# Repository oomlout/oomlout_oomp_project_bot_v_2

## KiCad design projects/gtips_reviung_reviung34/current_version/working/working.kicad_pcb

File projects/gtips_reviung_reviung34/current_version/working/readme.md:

# reviung
 
## summary 
* id: gtips_reviung_reviung34
* user: gtips
* name: reviung
* board: reviung34
* repo: https://github.com/gtips/reviung
* src_file_repo_kicad_pcb: reviung34/pcb/reviung34.kicad_pcb
* src_file_repo_kicad_pcb_link: https://github.com/gtips/reviung/tree/master/reviung34/pcb/reviung34.kicad_pcb

* src_file_repo_sch: reviung34/pcb/reviung34.sch
* src_file_repo_sch_link: https://github.com/gtips/reviung/tree/master/reviung34/pcb/reviung34.sch
* full details link: https://github.com/oomlout/oomlout_oomp_project_bot_v_2/tree/main/projects/gtips_reviung_reviung34/current_version/working  

## schematic  
  
[schematic (pdf)](working_schematic.pdf) 

## pcb  

[board (pdf)](working.pdf)  

## working_bom
| Id | Designator | Footprint | Quantity | Designation | Supplier and ref |  | None | 
| --- | --- | --- | --- | --- | --- | --- | --- | 
| 1 | RGB9,RGB1,RGB2,RGB3,RGB4,RGB5,RGB6,RGB7,RGB8 | LED_WS2812B_PLCC4_5.0x5.0mm_P3.2mm | 9 | WS2812B |  |  | [''] | 
| 2 | SW1,SW2,SW3,SW4,SW5,SW6,SW7,SW8,SW9,SW10,SW11,SW12,SW13,SW14,SW15,SW16,SW19,SW20,SW21,SW22,SW23,SW24,SW25,SW26,SW27,SW28,SW29,SW30,SW31,SW32,SW33,SW34 | MXOnly-1U-NoLED | 32 | SW_PUSH |  |  | [''] | 
| 3 | SW17 | MXOnly-1U-5pinRcut | 1 | SW_PUSH |  |  | [''] | 
| 4 | SW18 | MXOnly-1U-5pinLcut | 1 | SW_PUSH |  |  | [''] | 
| 5 | SW35 | MXOnly-2U-NoLED-or1Ux2 | 1 | SW_PUSH |  |  | [''] | 
| 6 | U1 | ProMicro | 1 | ProMicro |  |  | [''] | 
| 7 | H1,H2,H4,H3,H5,H7,H6,H8,H9 | HOLE_4.2mm | 9 | HOLE_4.2mm |  |  | [''] | 
| 8 | D1,D2,D3,D4,D5,D6,D7,D8,D9,D10,D11,D12,D13,D14,D15,D16,D17,D18,D19,D20,D21,D22,D23,D24,D25,D26,D27,D28,D29,D30,D31,D32,D33,D34 | D3_SMD_1side | 34 | 1N4148W |  |  | [''] | 
| 9 | RESET1 | ResetSW_1side | 1 | SW_PUSH |  |  | [''] | 
| 10 | G*** | QMK-x4-ver1 | 1 | LOGO |  |  | [''] | 
| 11 | G*** | reviung-logo | 1 | LOGO |  |  | [''] | 
| 12 | G*** | R-x4-ver1 | 1 | LOGO |  |  | [''] | 

## bom_schematic
| Ref | Qnty | Value | Cmp name | Footprint | Description | Vendor | DNP | 
| --- | --- | --- | --- | --- | --- | --- | --- | 
| D1, D2, D3, D4, D5, D6, D7, D8, D9, D10, D11, D12, D13, D14, D15, D16, D17, D18, D19, D20, D21, D22, D23, D24, D25, D26, D27, D28, D29, D30, D31, D32, D33, D34 | 34 | 1N4148W | 1N4148W | _reviung-kbd:D3_SMD_1side | 75V 0.15A Fast Switching Diode, SOD-123 |  |  | 
| RESET1 | 1 | SW_PUSH | SW_PUSH-_reviung-kbd | _reviung-kbd:ResetSW_1side |  |  |  | 
| RGB1, RGB2, RGB3, RGB4, RGB5, RGB6, RGB7, RGB8, RGB9 | 9 | WS2812B | WS2812B | _reviung-kbd:LED_WS2812B_PLCC4_5.0x5.0mm_P3.2mm | RGB LED with integrated controller |  |  | 
| SW1, SW2, SW3, SW4, SW5, SW6, SW7, SW8, SW9, SW10, SW11, SW12, SW13, SW14, SW15, SW16, SW19, SW20, SW21, SW22, SW23, SW24, SW25, SW26, SW27, SW28, SW29, SW30, SW31, SW32, SW33, SW34 | 32 | SW_PUSH | SW_PUSH-_reviung-kbd | _reviung-kbd:MXOnly-1U-NoLED |  |  |  | 
| SW17 | 1 | SW_PUSH | SW_PUSH-_reviung-kbd | _reviung-kbd:MXOnly-1U-5pinRcut |  |  |  | 
| SW18 | 1 | SW_PUSH | SW_PUSH-_reviung-kbd | _reviung-kbd:MXOnly-1U-5pinLcut |  |  |  | 
| SW35 | 1 | SW_PUSH | SW_PUSH-_reviung-kbd | _reviung-kbd:MXOnly-2U-NoLED-or1Ux2 |  |  |  | 
| U1 | 1 | ProMicro | ProMicro-_reviung-kbd | _reviung-kbd:ProMicro |  |  |  |

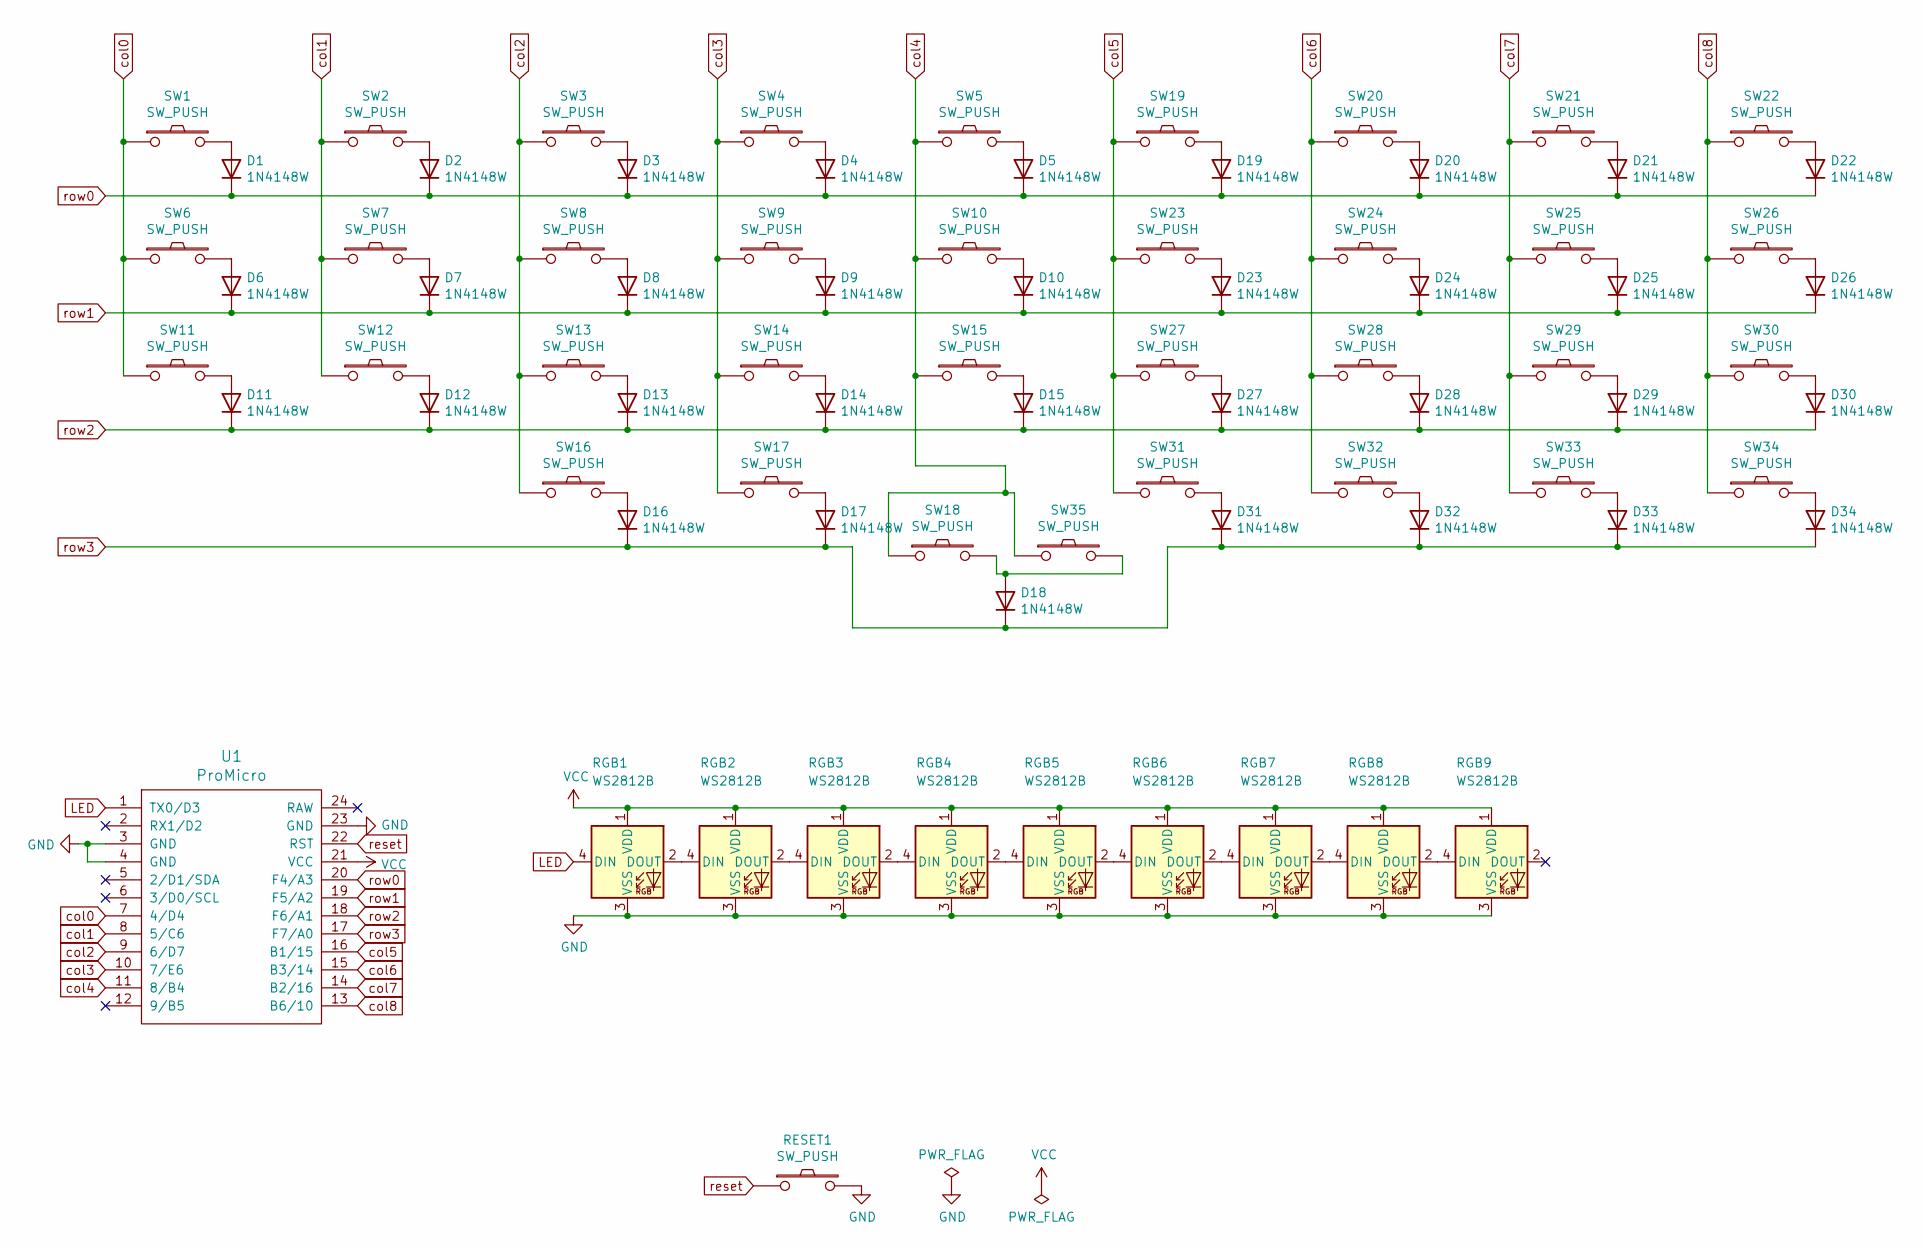
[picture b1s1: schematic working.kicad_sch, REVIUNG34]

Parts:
D1, D2, D3, D4, D5, D6, D7, D8, D9, D10, D11, D12, D13, D14, D15, D16, D17, D18, D19, D20, D21, D22, D23, D24, D25, D26, D27, D28, D29, D30, D31, D32, D33, D34: 1N4148W; D3_SMD_1side
RESET1: SW_PUSH; ResetSW_1side
RGB1, RGB2, RGB3, RGB4, RGB5, RGB6, RGB7, RGB8, RGB9: WS2812B; LED_WS2812B_PLCC4_5.0x5.0mm_P3.2mm
SW1, SW2, SW3, SW4, SW5, SW6, SW7, SW8, SW9, SW10, SW11, SW12, SW13, SW14, SW15, SW16, SW19, SW20, SW21, SW22, SW23, SW24, SW25, SW26, SW27, SW28, SW29, SW30, SW31, SW32, SW33, SW34: SW_PUSH; MXOnly-1U-NoLED
SW17: SW_PUSH; MXOnly-1U-5pinRcut
SW18: SW_PUSH; MXOnly-1U-5pinLcut
SW35: SW_PUSH; MXOnly-2U-NoLED-or1Ux2
U1: ProMicro

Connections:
GND: RESET1.2, RGB1.3 (VSS), RGB2.3 (VSS), RGB3.3 (VSS), RGB4.3 (VSS), RGB5.3 (VSS), RGB6.3 (VSS), RGB7.3 (VSS), RGB8.3 (VSS), RGB9.3 (VSS), U1.3 (GND), U1.4 (GND), U1.23 (GND)
LED: RGB1.4 (DIN), U1.1 (TX0/D3)
unnamed: D1.2 (A), SW1.2
unnamed: D2.2 (A), SW2.2
unnamed: D3.2 (A), SW3.2
unnamed: D4.2 (A), SW4.2
unnamed: D5.2 (A), SW5.2
unnamed: D6.2 (A), SW6.2
unnamed: D7.2 (A), SW7.2
unnamed: D8.2 (A), SW8.2
unnamed: D9.2 (A), SW9.2
unnamed: D10.2 (A), SW10.2
unnamed: D11.2 (A), SW11.2
unnamed: D12.2 (A), SW12.2
unnamed: D13.2 (A), SW13.2
unnamed: D14.2 (A), SW14.2
unnamed: D15.2 (A), SW15.2
unnamed: D16.2 (A), SW16.2
unnamed: D17.2 (A), SW17.2
unnamed: D18.2 (A), SW18.2, SW35.2
unnamed: D19.2 (A), SW19.2
unnamed: D20.2 (A), SW20.2
unnamed: D21.2 (A), SW21.2
unnamed: D22.2 (A), SW22.2
unnamed: D23.2 (A), SW23.2
unnamed: D24.2 (A), SW24.2
unnamed: D25.2 (A), SW25.2
unnamed: D26.2 (A), SW26.2
unnamed: D27.2 (A), SW27.2
unnamed: D28.2 (A), SW28.2
unnamed: D29.2 (A), SW29.2
unnamed: D30.2 (A), SW30.2
unnamed: D31.2 (A), SW31.2
unnamed: D32.2 (A), SW32.2
unnamed: D33.2 (A), SW33.2
unnamed: D34.2 (A), SW34.2
unnamed: RGB1.2 (DOUT), RGB2.4 (DIN)
unnamed: RGB2.2 (DOUT), RGB3.4 (DIN)
unnamed: RGB3.2 (DOUT), RGB4.4 (DIN)
unnamed: RGB4.2 (DOUT), RGB5.4 (DIN)
unnamed: RGB5.2 (DOUT), RGB6.4 (DIN)
unnamed: RGB6.2 (DOUT), RGB7.4 (DIN)
unnamed: RGB7.2 (DOUT), RGB8.4 (DIN)
unnamed: RGB8.2 (DOUT), RGB9.4 (DIN)
VCC: RGB1.1 (VDD), RGB2.1 (VDD), RGB3.1 (VDD), RGB4.1 (VDD), RGB5.1 (VDD), RGB6.1 (VDD), RGB7.1 (VDD), RGB8.1 (VDD), RGB9.1 (VDD), U1.21 (VCC)
col0: SW1.1, SW6.1, SW11.1, U1.7 (4/D4)
col1: SW2.1, SW7.1, SW12.1, U1.8 (5/C6)
col2: SW3.1, SW8.1, SW13.1, SW16.1, U1.9 (6/D7)
col3: SW4.1, SW9.1, SW14.1, SW17.1, U1.10 (7/E6)
col4: SW5.1, SW10.1, SW15.1, SW18.1, SW35.1, U1.11 (8/B4)
col5: SW19.1, SW23.1, SW27.1, SW31.1, U1.16 (B1/15)
col6: SW20.1, SW24.1, SW28.1, SW32.1, U1.15 (B3/14)
col7: SW21.1, SW25.1, SW29.1, SW33.1, U1.14 (B2/16)
col8: SW22.1, SW26.1, SW30.1, SW34.1, U1.13 (B6/10)
reset: RESET1.1, U1.22 (RST)
row0: D1.1 (K), D2.1 (K), D3.1 (K), D4.1 (K), D5.1 (K), D19.1 (K), D20.1 (K), D21.1 (K), D22.1 (K), U1.20 (F4/A3)
row1: D6.1 (K), D7.1 (K), D8.1 (K), D9.1 (K), D10.1 (K), D23.1 (K), D24.1 (K), D25.1 (K), D26.1 (K), U1.19 (F5/A2)
row2: D11.1 (K), D12.1 (K), D13.1 (K), D14.1 (K), D15.1 (K), D27.1 (K), D28.1 (K), D29.1 (K), D30.1 (K), U1.18 (F6/A1)
row3: D16.1 (K), D17.1 (K), D18.1 (K), D31.1 (K), D32.1 (K), D33.1 (K), D34.1 (K), U1.17 (F7/A0)

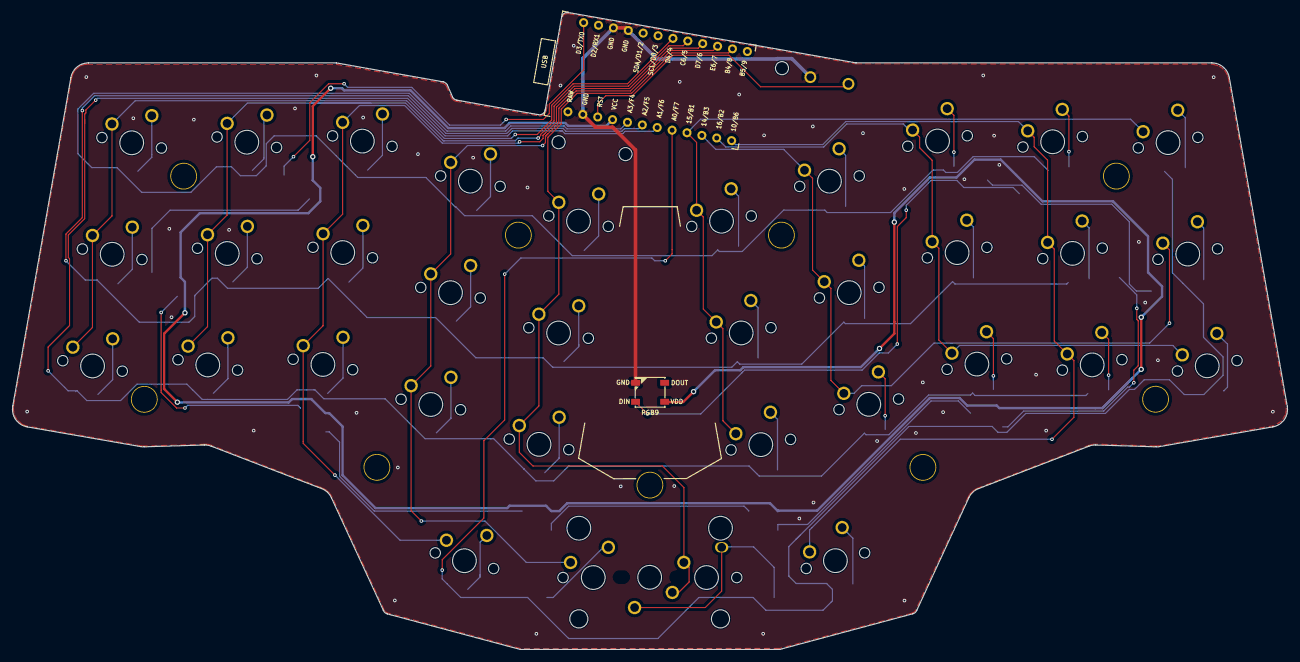
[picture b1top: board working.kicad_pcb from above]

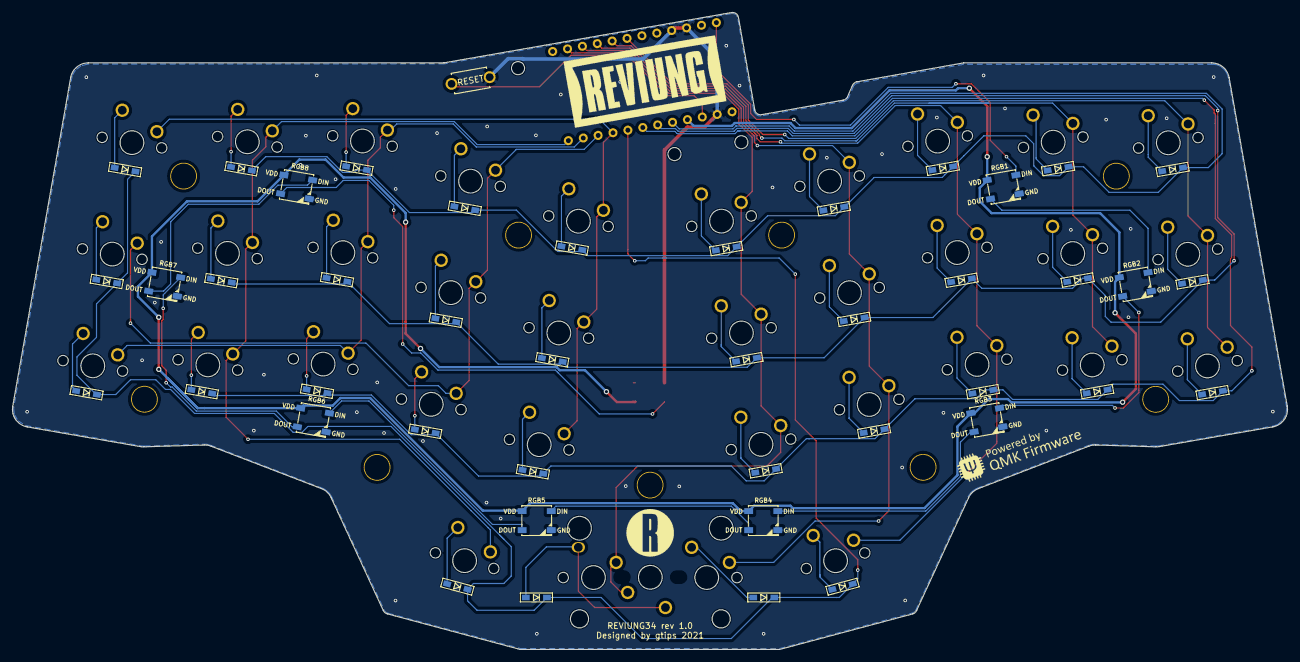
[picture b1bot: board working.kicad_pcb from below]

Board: 2 copper layers, 214.3 x 107.1 mm, 92 parts (43 on the bottom side), 59 nets.

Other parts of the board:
H1, H2, H3, H4, H5, H6, H7, H8, H9: HOLE_4.2mm
Ref**: Val**; HOLE_2.2mm
Ref**#2, Ref**#3: Val**; HOLE_2.2mm

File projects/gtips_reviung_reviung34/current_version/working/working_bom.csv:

"Id";"Designator";"Footprint";"Quantity";"Designation";"Supplier and ref";
1;"RGB9,RGB1,RGB2,RGB3,RGB4,RGB5,RGB6,RGB7,RGB8";"LED_WS2812B_PLCC4_5.0x5.0mm_P3.2mm";9;"WS2812B";;;
2;"SW1,SW2,SW3,SW4,SW5,SW6,SW7,SW8,SW9,SW10,SW11,SW12,SW13,SW14,SW15,SW16,SW19,SW20,SW21,SW22,SW23,SW24,SW25,SW26,SW27,SW28,SW29,SW30,SW31,SW32,SW33,SW34";"MXOnly-1U-NoLED";32;"SW_PUSH";;;
3;"SW17";"MXOnly-1U-5pinRcut";1;"SW_PUSH";;;
4;"SW18";"MXOnly-1U-5pinLcut";1;"SW_PUSH";;;
5;"SW35";"MXOnly-2U-NoLED-or1Ux2";1;"SW_PUSH";;;
6;"U1";"ProMicro";1;"ProMicro";;;
7;"H1,H2,H4,H3,H5,H7,H6,H8,H9";"HOLE_4.2mm";9;"HOLE_4.2mm";;;
8;"D1,D2,D3,D4,D5,D6,D7,D8,D9,D10,D11,D12,D13,D14,D15,D16,D17,D18,D19,D20,D21,D22,D23,D24,D25,D26,D27,D28,D29,D30,D31,D32,D33,D34";"D3_SMD_1side";34;"1N4148W";;;
9;"RESET1";"ResetSW_1side";1;"SW_PUSH";;;
10;"G***";"QMK-x4-ver1";1;"LOGO";;;
11;"G***";"reviung-logo";1;"LOGO";;;
12;"G***";"R-x4-ver1";1;"LOGO";;;
